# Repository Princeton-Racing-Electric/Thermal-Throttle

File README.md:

# Thermal Throttle PCB repo

(for VCU team)

## Pics

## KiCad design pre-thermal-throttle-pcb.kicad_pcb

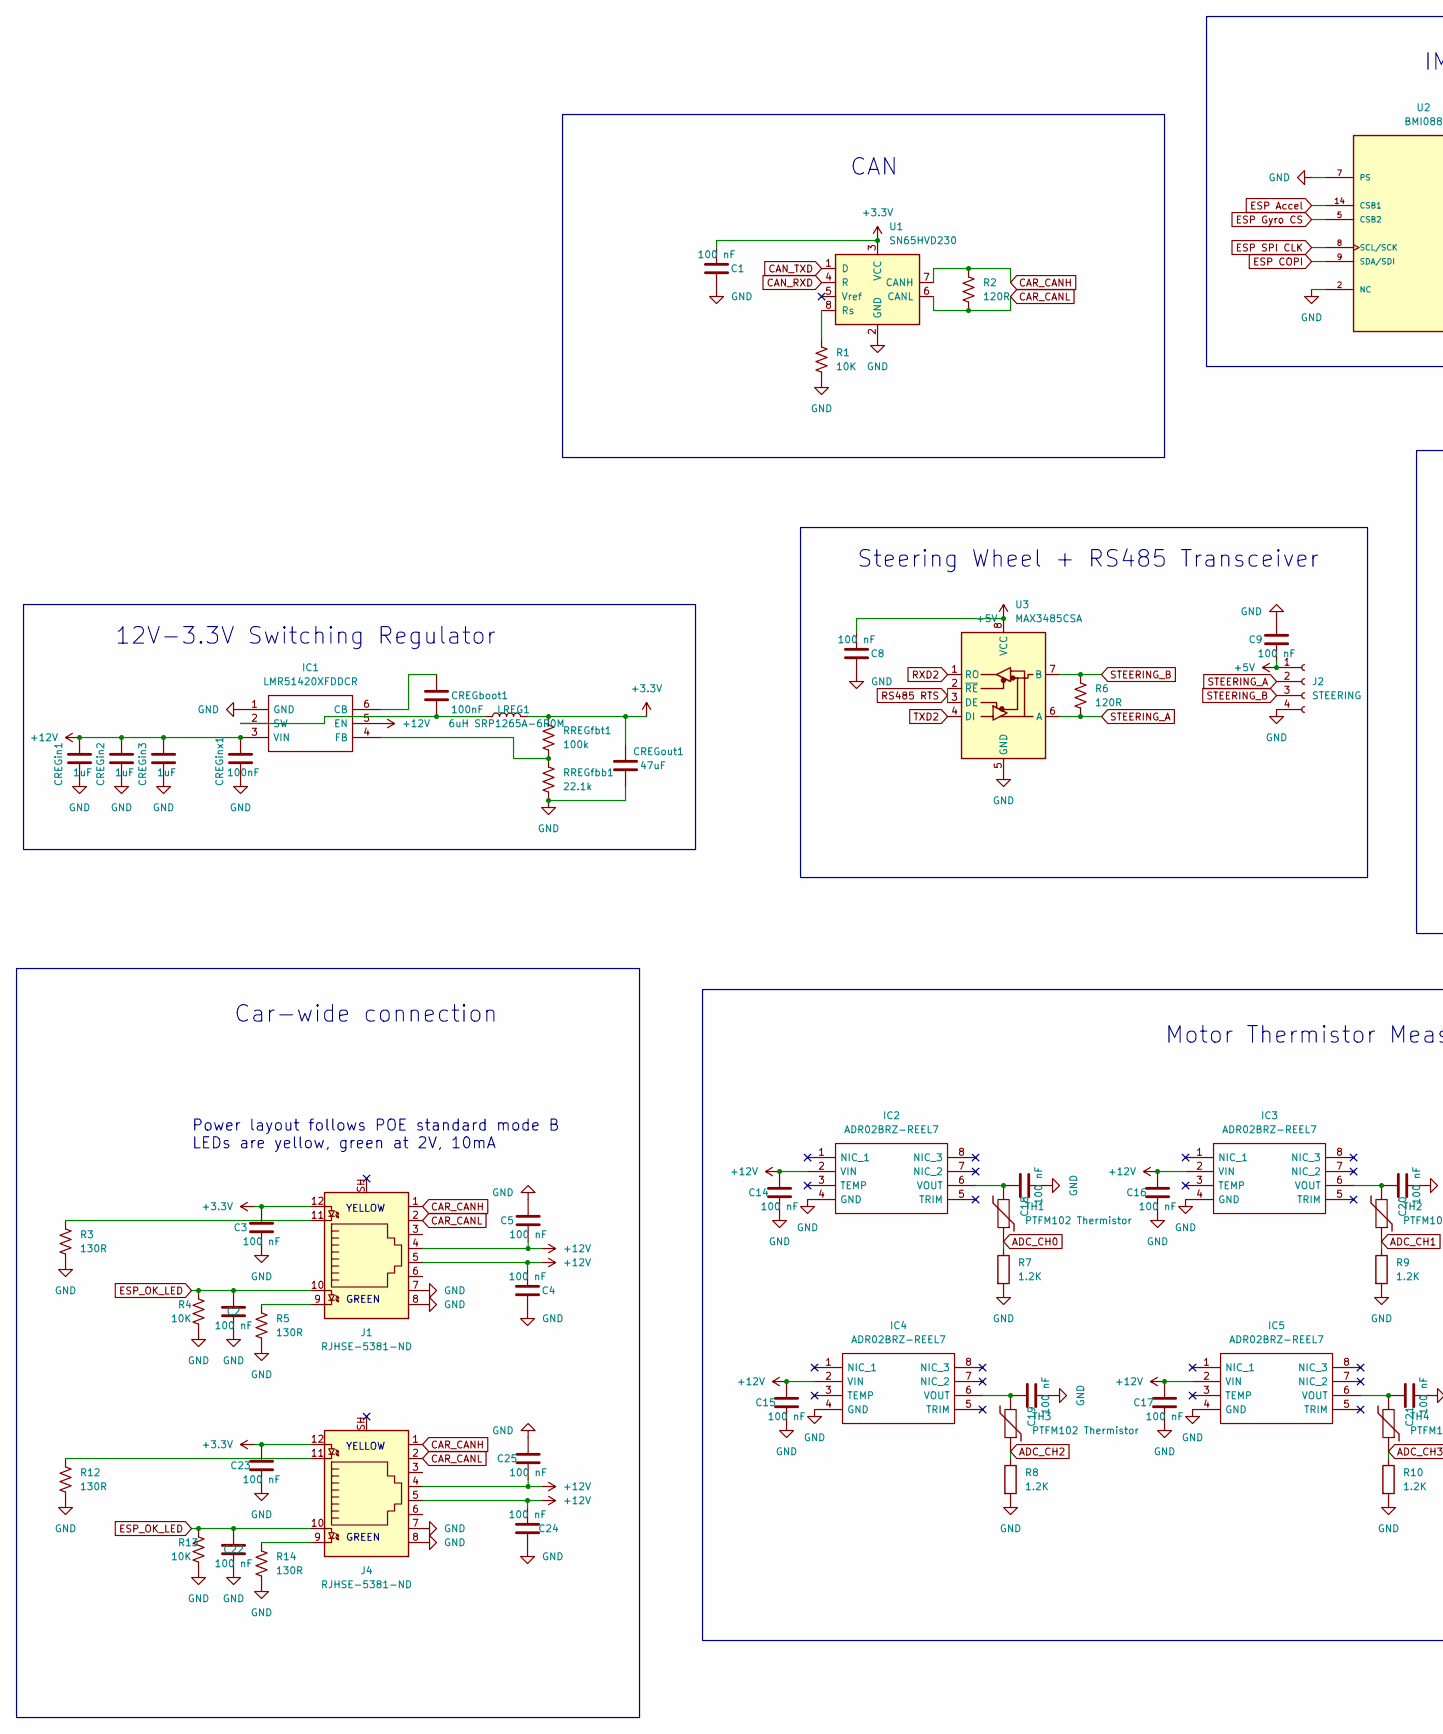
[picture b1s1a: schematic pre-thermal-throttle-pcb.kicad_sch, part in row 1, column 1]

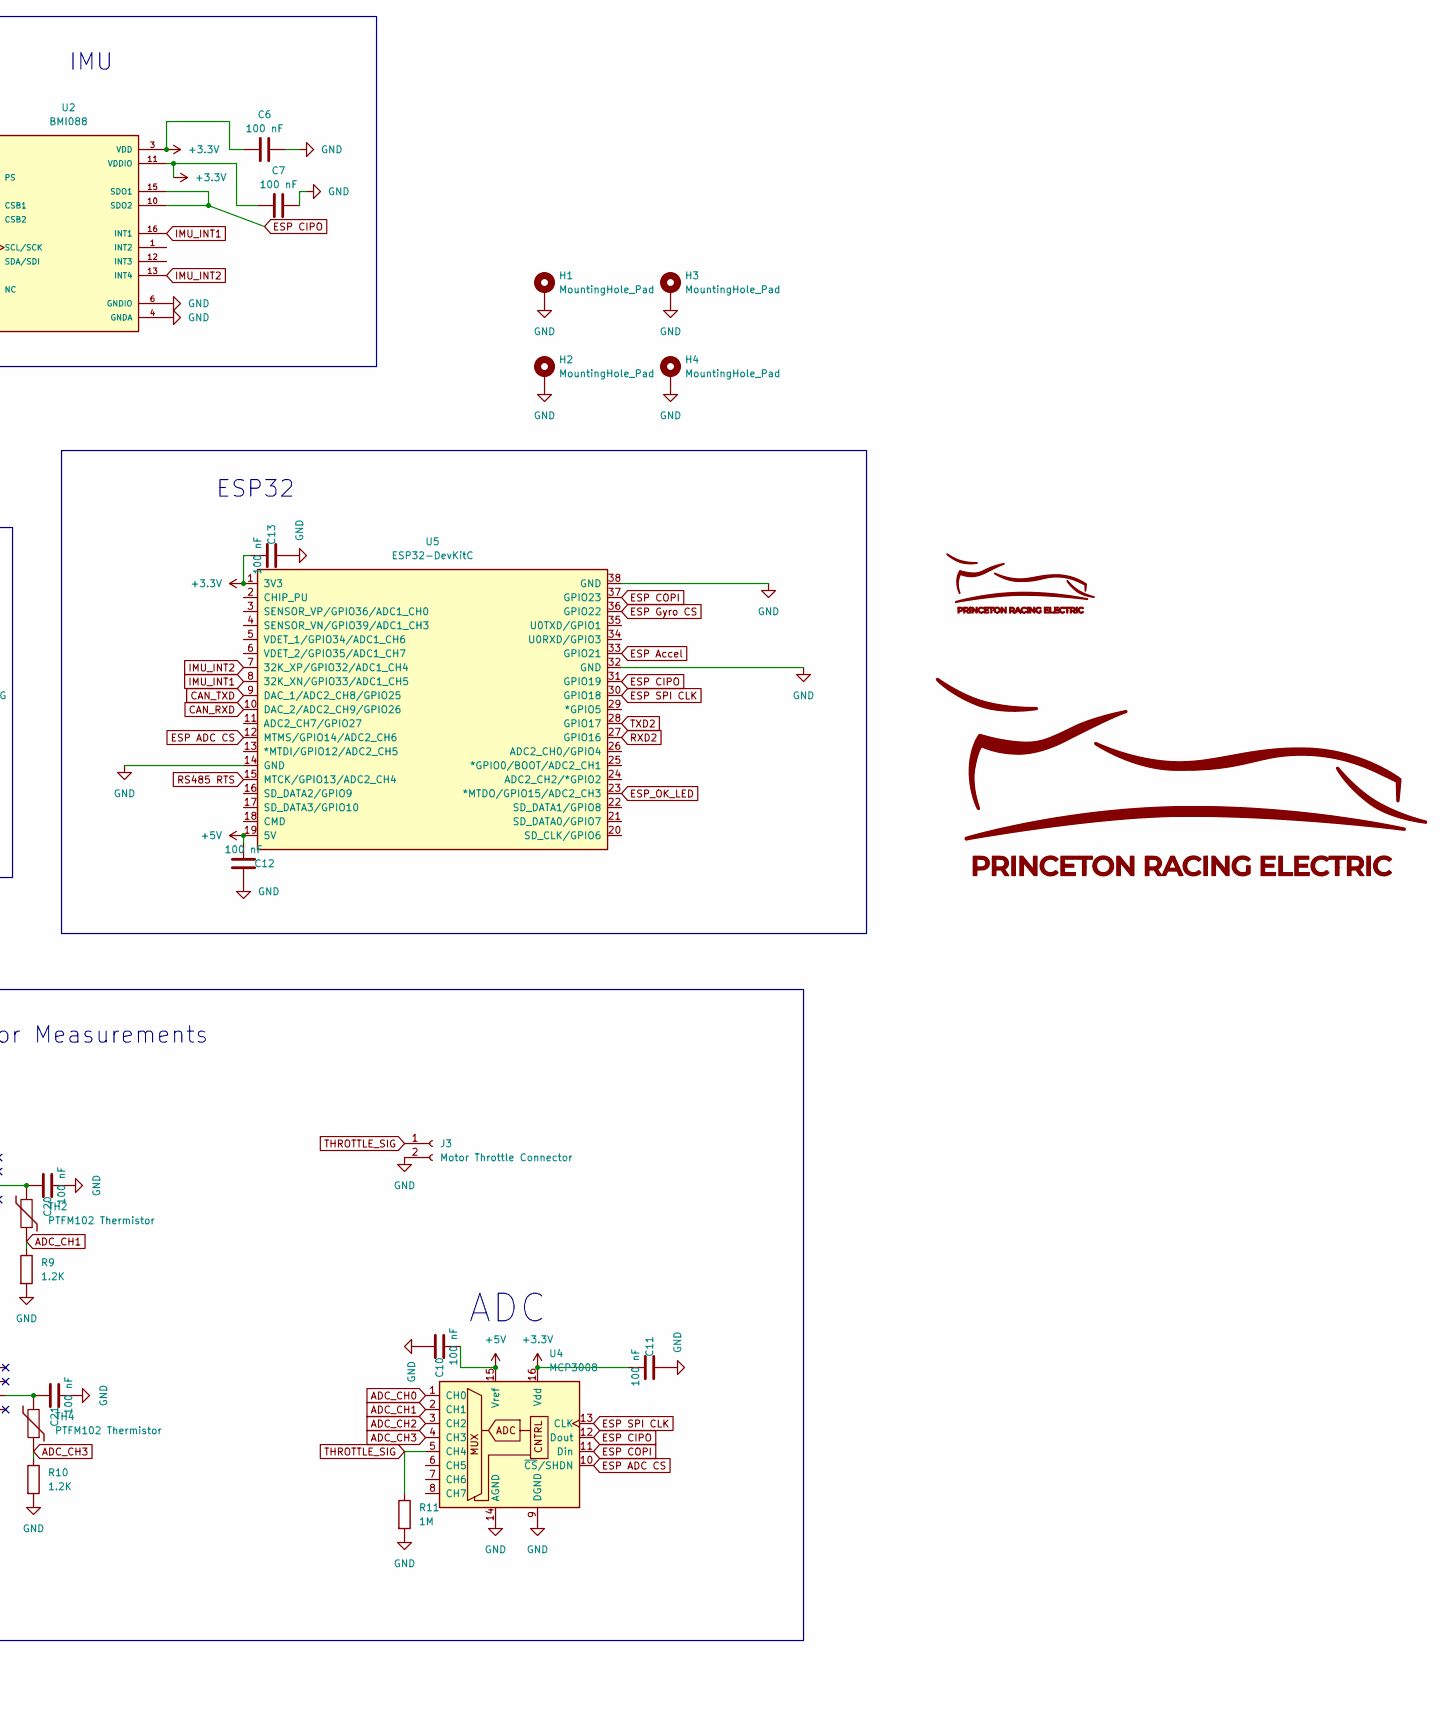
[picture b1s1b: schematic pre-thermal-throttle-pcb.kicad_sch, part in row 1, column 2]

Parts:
C1, C2, C3, C4, C5, C6, C7, C8, C9, C10, C11, C12, C13, C14, C15, C16, C17, C18, C19, C20, C21, C22, C23, C24, C25: 100 nF; C_0805_2012Metric
CREGboot1: 100nF; C_0805_2012Metric
CREGin1, CREGin2, CREGin3: 1uF; C_0805_2012Metric
CREGinx1: 100nF; C_0805_2012Metric
CREGout1: 47uF; C_0805_2012Metric
G1: LOGO; pre_logo_medium
G2: LOGO; pre_logo_big
H1, H2, H3, H4: MountingHole_Pad; MountingHole_3mm_Pad_Via
IC1: LMR51420XFDDCR; SOT95P280X110-6N; Mouser Part Number 595-LMR51420XFDDCR
IC2, IC3, IC4, IC5: ADR02BRZ-REEL7; SOIC127P600X175-8N; Mouser Part Number 584-ADR02BRZ-R7
J1, J4: RJHSE-5381-ND; RJ45_Amphenol_RJHSE538X
J2: STEERING; JST_XH_B4B-XH-A_1x04_P2.50mm_Vertical
J3: Motor Throttle Connector; JST_XH_B2B-XH-A_1x02_P2.50mm_Vertical
LREG1: 6uH SRP1265A-6R0M; L_Bourns_SRP1260A
R1, R4, R13: 10K; R_0805_2012Metric
R2, R6: 120R; R_Axial_DIN0309_L9.0mm_D3.2mm_P15.24mm_Horizontal
R3, R5, R12, R14: 130R; R_0805_2012Metric
R7, R8, R9, R10: 1.2K; R_0805_2012Metric
R11: 1M; R_0805_2012Metric
RREGfbb1: 22.1k; R_0805_2012Metric
RREGfbt1: 100k; R_0805_2012Metric
TH1, TH2, TH3, TH4: PTFM102 Thermistor; JST_XH_B2B-XH-A_1x02_P2.50mm_Vertical
U1: SN65HVD230; SOIC-8_3.9x4.9mm_P1.27mm
U2: BMI088; PQFN50P450X300X100-16N
U3: MAX3485CSA; SOIC-8-1EP_3.9x4.9mm_P1.27mm_EP2.41x3.81mm_ThermalVias
U4: MCP3008; DIP-16_W7.62mm
U5: ESP32-DevKitC

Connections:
+3.3V: C1.1, C3.2, C6.1, C7.1, C11.1, C13.1, C23.2, CREGout1.1, J1.12, J4.12, LREG1.2, RREGfbt1.1, U1.3 (VCC), U2.3 (VDD), U2.11 (VDDIO), U4.16 (Vdd), U5.1 (3V3)
+5V: C8.1, C9.1, C10.1, C12.1, J2.1, U3.8 (VCC), U4.15 (Vref), U5.19 (5V)
+12V: C4.1, C5.1, C14.2, C15.2, C16.2, C17.2, C24.1, C25.1, CREGin1.1, CREGin2.1, CREGin3.1, CREGinx1.1, IC1.3 (VIN), IC1.5 (EN), IC2.2 (VIN), IC3.2 (VIN), IC4.2 (VIN), IC5.2 (VIN), J1.4, J1.5, J4.4, J4.5
ADC_CH0: R7.1, TH1.1, U4.1 (CH0)
ADC_CH1: R9.1, TH2.1, U4.2 (CH1)
ADC_CH2: R8.1, TH3.1, U4.3 (CH2)
ADC_CH3: R10.1, TH4.1, U4.4 (CH3)
CAN_RXD: U1.4 (R), U5.10 (DAC_2/ADC2_CH9/GPIO26)
CAN_TXD: U1.1 (D), U5.9 (DAC_1/ADC2_CH8/GPIO25)
CAR_CANH: J1.1, J4.1, R2.1, U1.7 (CANH)
CAR_CANL: J1.2, J4.2, R2.2, U1.6 (CANL)
ESP ADC CS: U4.10 (~CS/SHDN), U5.12 (MTMS/GPIO14/ADC2_CH6)
ESP Accel: U2.14 (CSB1), U5.33 (GPIO21)
ESP CIPO: U2.10 (SDO2), U2.15 (SDO1), U4.12 (Dout), U5.31 (GPIO19)
ESP COPI: U2.9 (SDA/SDI), U4.11 (Din), U5.37 (GPIO23)
ESP Gyro CS: U2.5 (CSB2), U5.36 (GPIO22)
ESP SPI CLK: U2.8 (SCL/SCK), U4.13 (CLK), U5.30 (GPIO18)
ESP_OK_LED: C2.2, C22.2, J1.10, J4.10, R4.1, R13.1, U5.23 (*MTDO/GPIO15/ADC2_CH3)
GND: C1.2, C2.1, C3.1, C4.2, C5.2, C6.2, C7.2, C8.2, C9.2, C10.2, C11.2, C12.2, C13.2, C14.1, C15.1, C16.1, C17.1, C18.1, C19.1, C20.1, C21.1, C22.1, C23.1, C24.2, C25.2, CREGin1.2, CREGin2.2, CREGin3.2, CREGinx1.2, CREGout1.2, H1.1, H2.1, H3.1, H4.1, IC1.1 (GND), IC2.4 (GND), IC3.4 (GND), IC4.4 (GND), IC5.4 (GND), J1.7, J1.8, J2.4, J3.2, J4.7, J4.8, R1.2, R3.1, R4.2, R5.1, R7.2, R8.2, R9.2, R10.2, R11.2, R12.1, R13.2, R14.1, RREGfbb1.2, U1.2 (GND), U2.2 (NC), U2.4 (GNDA), U2.6 (GNDIO), U2.7 (PS), U3.5 (GND), U4.9 (DGND), U4.14 (AGND), U5.14 (GND), U5.32 (GND), U5.38 (GND)
IMU_INT1: U2.16 (INT1), U5.8 (32K_XN/GPIO33/ADC1_CH5)
IMU_INT2: U2.13 (INT4), U5.7 (32K_XP/GPIO32/ADC1_CH4)
unnamed: C18.2, IC2.6 (VOUT), TH1.2
unnamed: C19.2, IC4.6 (VOUT), TH3.2
unnamed: C20.2, IC3.6 (VOUT), TH2.2
unnamed: C21.2, IC5.6 (VOUT), TH4.2
unnamed: CREGboot1.1, IC1.6 (CB)
unnamed: CREGboot1.2, IC1.2 (SW), LREG1.1
unnamed: IC1.4 (FB), RREGfbb1.1, RREGfbt1.2
unnamed: J1.9, R5.2
unnamed: J1.11, R3.2
unnamed: J4.9, R14.2
unnamed: J4.11, R12.2
unnamed: R1.1, U1.8 (Rs)
RS485 RTS: U3.2 (~RE), U3.3 (DE), U5.15 (MTCK/GPIO13/ADC2_CH4)
RXD2: U3.1 (RO), U5.27 (GPIO16)
STEERING_A: J2.2, R6.2, U3.6 (A)
STEERING_B: J2.3, R6.1, U3.7 (B)
THROTTLE_SIG: J3.1, R11.1, U4.5 (CH4)
TXD2: U3.4 (DI), U5.28 (GPIO17)

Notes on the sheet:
12V-3.3V Switching Regulator
IMU
ADC
YELLOW
Steering Wheel + RS485 Transceiver
ESP32
GREEN
Power layout follows POE standard mode B LEDs are yellow, green at 2V, 10mA
CAN
Motor Thermistor Measurements
Car-wide connection

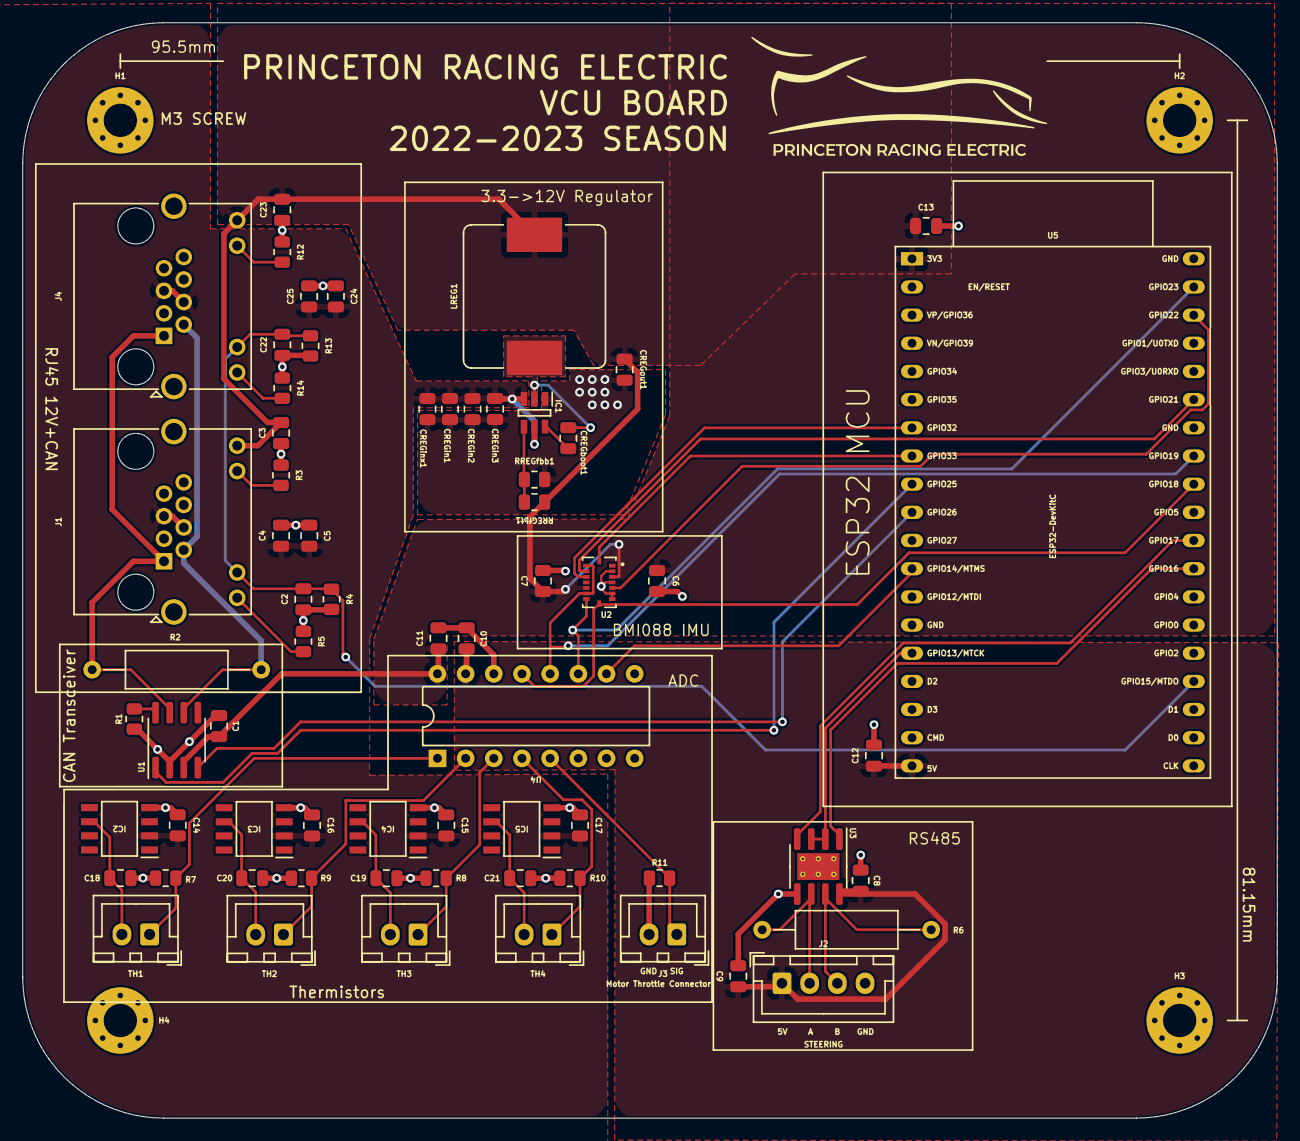
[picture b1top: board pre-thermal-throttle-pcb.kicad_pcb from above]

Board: 2 copper layers, 113.1 x 98.8 mm, 72 parts (1 on the bottom side), 39 nets.

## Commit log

2023-02-05 Add initial schematics
2023-02-12 Add in thermistor and ADC
2023-02-12 Label stuff
2023-02-19 Add switching regulator circuit basic schematic, values need compute
2023-02-24 Setup footprints and add bypass caps
2023-02-25 Finish part selection
2023-02-26 Add extra rj45 for CAN splice and connect imu ints
2023-03-03 Finish most traces
2023-03-05 Hopefully finished?
2023-03-05 Muh silkscreen
2023-03-05 Add gerbers
